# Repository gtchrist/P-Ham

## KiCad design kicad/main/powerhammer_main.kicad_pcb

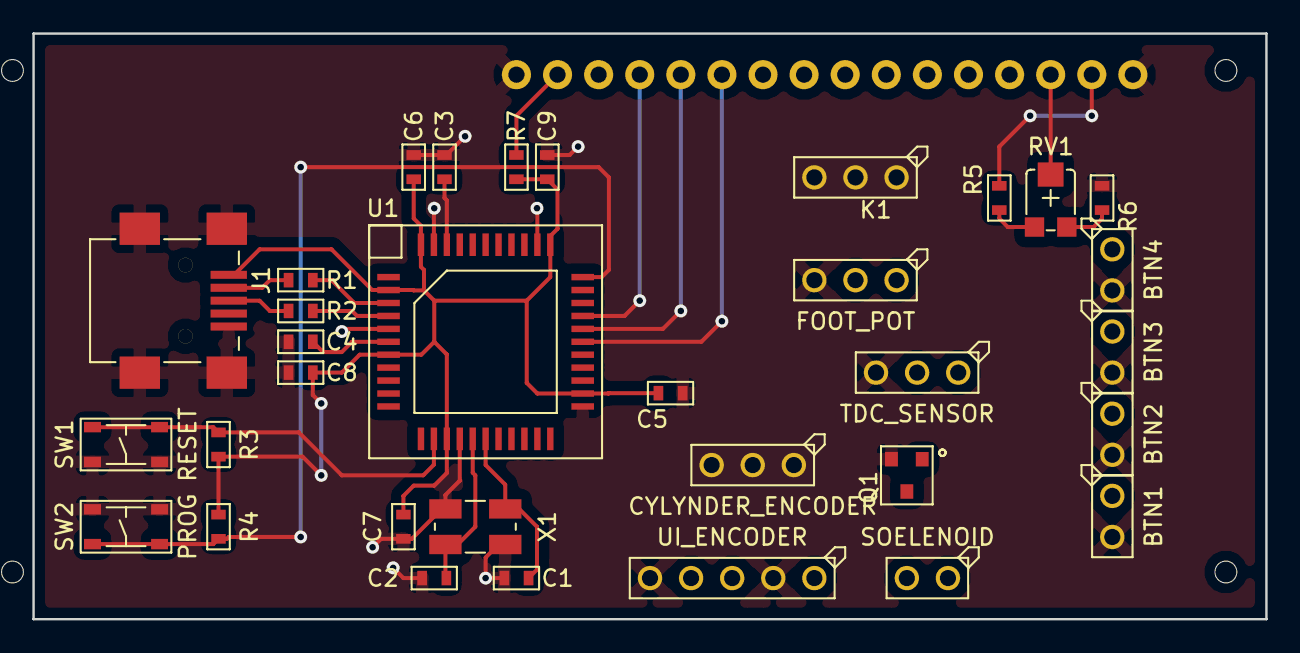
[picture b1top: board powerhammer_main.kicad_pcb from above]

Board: 2 copper layers, 76.2 x 36.2 mm, 34 parts (1 on the bottom side), 37 nets.

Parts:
C1, C2: 8pF; MF_Passives-C0603
C3, C4: 1uF; MF_Passives-C0603
C5, C6, C7, C8, C9: 0.1uF; MF_Passives-C0603
DS1: HD44780
J1: USB_MINI_RIGHT; MF_Connectors-MINIUSB-RIGHT
K1: SERVO; MF_Connectors-PTH_2.54MM_01X03
K2: FOOT_POT; MF_Connectors-PTH_2.54MM_01X03
K3: TDC_SENSOR; MF_Connectors-PTH_2.54MM_01X03
K4: SOELENOID; MF_Connectors-PTH_2.54MM_01X02
K5: BTN1; MF_Connectors-PTH_2.54MM_01X02
K6: BTN2; MF_Connectors-PTH_2.54MM_01X02
K7: BTN3; MF_Connectors-PTH_2.54MM_01X02
K8: BTN4; MF_Connectors-PTH_2.54MM_01X02
Q1: MOSFET-SOT-23-3; MF_Discrete_Semiconductor-SOT-23-3
R1, R2: 22; MF_Passives-R0603
R3, R4: 10k; MF_Passives-R0603
R5: 100k; MF_Passives-R0603
R6, R7: 1k; MF_Passives-R0603
RV1: POTENTIOMETER; MF_Passives-TC33
SW1: RESET; MF_Switches-TACT4.2MM
SW2: PROG; MF_Switches-TACT4.2MM
SW3: CYLYNDER_ENCODER; MF_Connectors-PTH_2.54MM_01X03
SW4: UI_ENCODER; MF_Connectors-PTH_2.54MM_01X05
U1: ATmega32U4-AU; MF_IC_Digital-TQFP44
X1: CRYSTAL_SMD_4PIN; MF_Frequency_Control-5MMX3.2MM

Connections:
+5V: C5.2, C6.2, C7.2, C8.2, C9.2, DS1.2, J1.1, K1.1, K2.1, R3.1, R4.1, R5.2, R7.1, U1.2, U1.7, U1.14, U1.24, U1.34, U1.44
+12V: K3.1, K4.1
GND: C1.1, C2.1, C3.2, C4.1, C5.1, C6.1, C7.1, C8.1, C9.1, DS1.1, DS1.5, DS1.16, J1.5, J1.S1, J1.S2, J1.S3, J1.S4, K1.3, K2.3, K3.3, K5.2, K6.2, K7.2, K8.2, Q1.2, R6.1, SW1.3, SW1.4, SW2.1, SW2.2, SW3.2, SW4.2, SW4.5, U1.5, U1.15, U1.23, U1.35, U1.43, X1.2, X1.4
unnamed: C1.2, U1.17, X1.3
unnamed: C2.2, U1.16, X1.1
unnamed: C3.1, U1.42
unnamed: C4.2, U1.6
unnamed: DS1.3, RV1.2
unnamed: DS1.4, U1.37
unnamed: DS1.6, U1.36
unnamed: DS1.11, U1.28
unnamed: DS1.12, U1.29
unnamed: DS1.13, U1.30
unnamed: DS1.14, U1.12
unnamed: DS1.15, R7.2
unnamed: J1.2, R1.2
unnamed: J1.3, R2.2
unnamed: K1.2, U1.32
unnamed: K2.2, U1.41
unnamed: K3.2, U1.40
unnamed: K4.2, Q1.3
unnamed: K5.1, U1.18
unnamed: K6.1, U1.19
unnamed: K7.1, U1.20
unnamed: K8.1, U1.21
unnamed: Q1.1, U1.39
unnamed: R1.1, U1.3
unnamed: R2.1, U1.4
unnamed: R3.2, SW1.1, SW1.2, U1.13
unnamed: R4.2, SW2.3, SW2.4, U1.33
unnamed: R5.1, RV1.1
unnamed: R6.2, RV1.3
unnamed: SW3.1, U1.8
unnamed: SW3.3, U1.9
unnamed: SW4.1, U1.10
unnamed: SW4.3, U1.11
unnamed: SW4.4, U1.31

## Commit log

2018-09-17 committing some base files for the program... much more work required
2018-09-17 Output ADC value to serial port for debugging
2018-09-17 updating gitignore
2018-09-17 Added in servo control value which maps to potentiometer value. Untested but compiles.
2018-09-18 Adding kicad stuff
2018-09-18 verifying that servo works as expected. Minor changes to build script to support linux dfu-programmer. Remove build folder from git.
2018-09-19 removed gitter from servo and added documentation
2018-09-19 Updated schematic
2018-09-19 Working on board layout
2018-10-06 sharing
2019-01-21 Changes made while on team viewer with Wyatt to get connected and running.
2019-09-12 Copying newer included libraries from microcontroller-projects
2019-09-12 Adding test / sample programs
2019-09-13 this was modified while Wyatt was at my house
